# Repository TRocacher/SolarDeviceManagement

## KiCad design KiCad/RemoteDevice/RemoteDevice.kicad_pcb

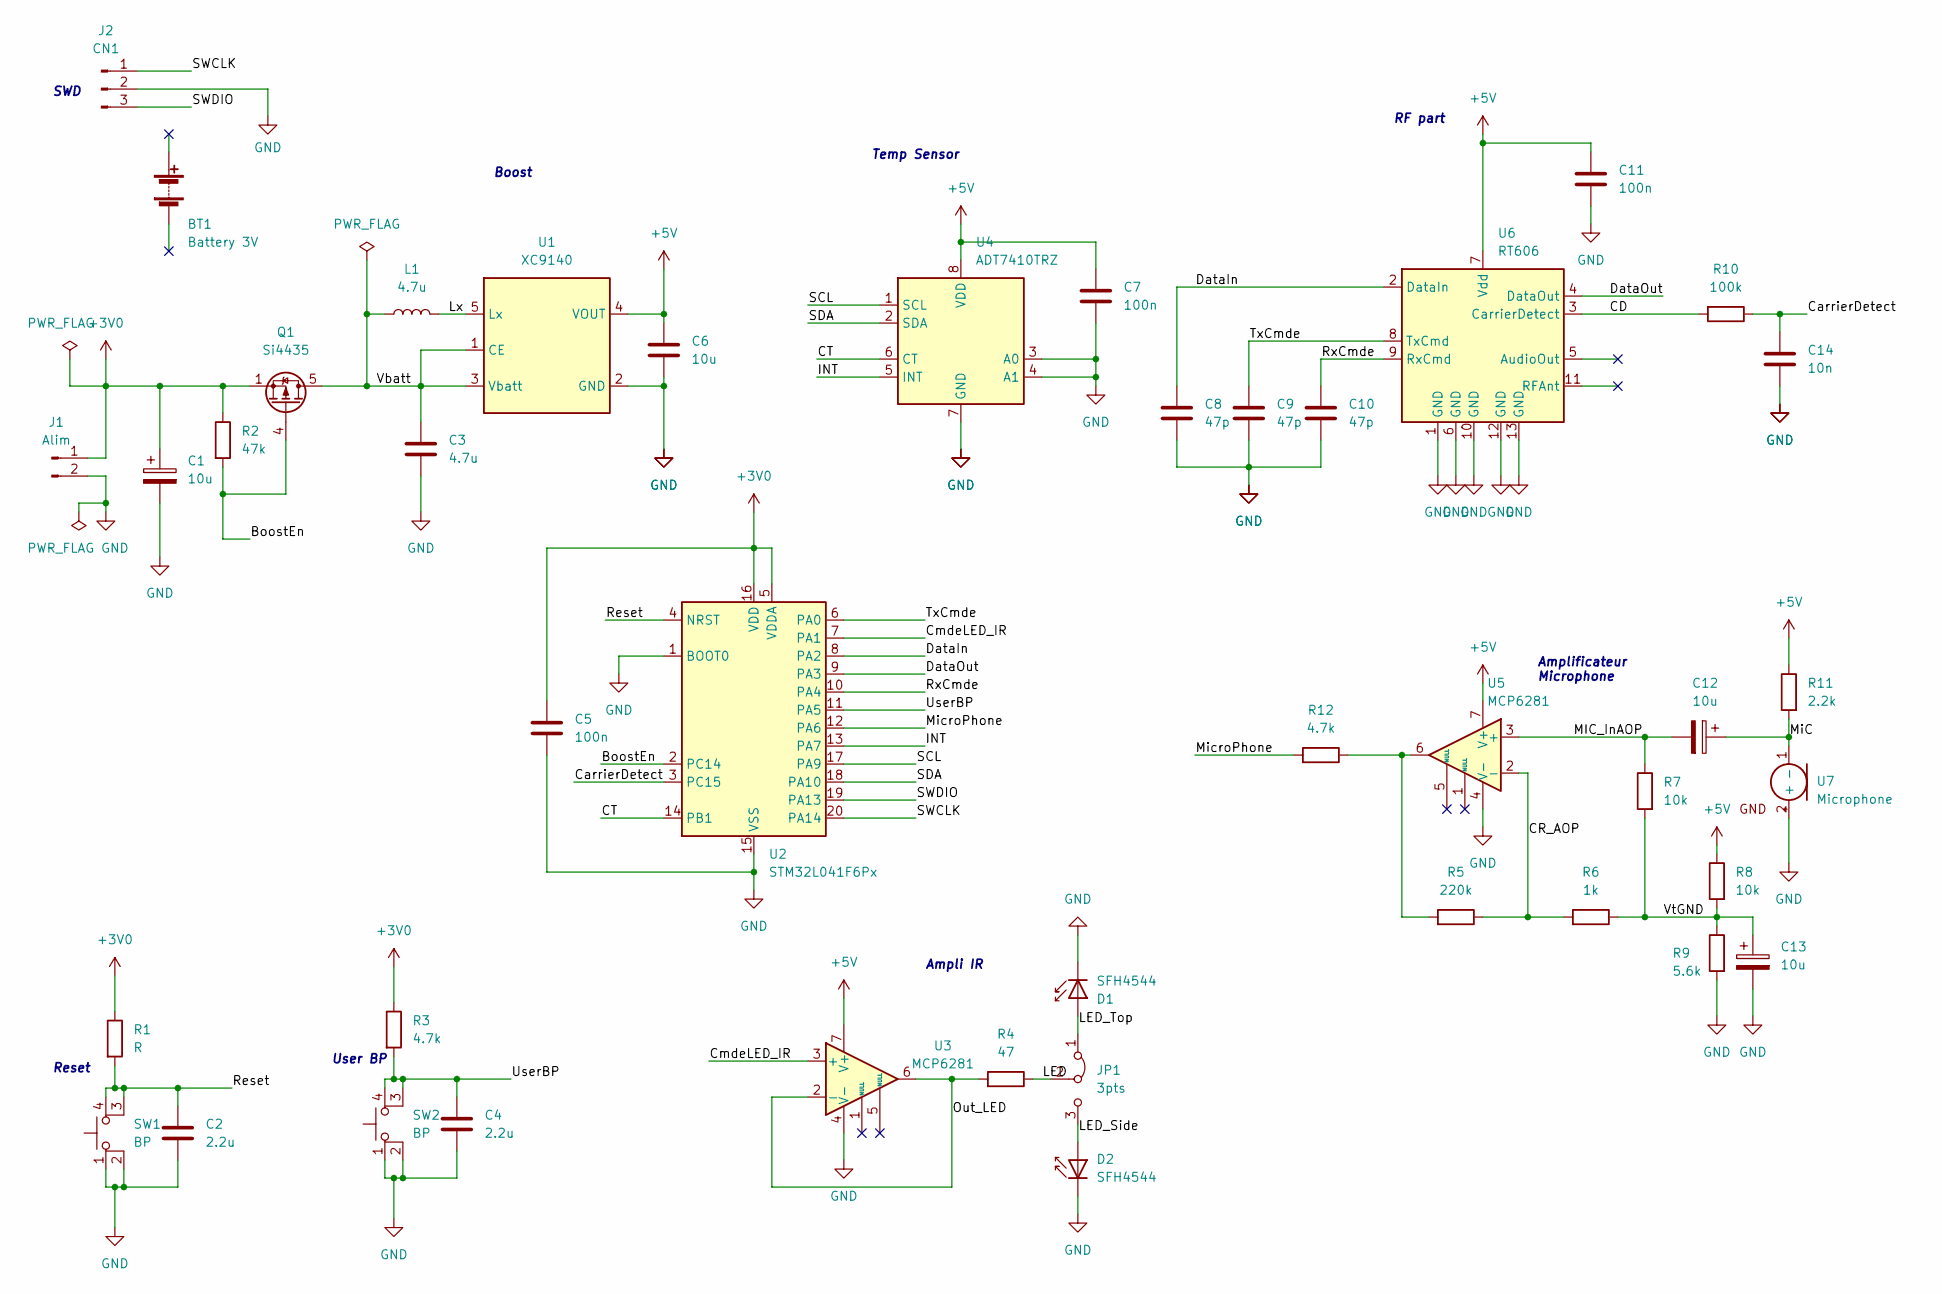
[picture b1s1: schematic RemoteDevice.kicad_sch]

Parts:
BT1: Battery 3V; BatteryHolder_Keystone_2468_2xAAA
C1, C12, C13: 10u; CP_EIA-7132-20_AVX-U
C2, C4: 2.2u; C_1812_4532Metric
C3: 4.7u; C_1812_4532Metric
C5, C7, C11: 100n; C_1206_3216Metric
C6: 10u; C_1812_4532Metric
C8, C9, C10: 47p; C_0805_2012Metric
C14: 10n; C_1206_3216Metric
D1, D2: SFH4544; LED_D5.0mm_IRGrey
J1: Alim; PinHeader2pts
J2: CN1; PinHeader3pts
JP1: 3pts; PinHeader3pts
L1: 4.7u; L_Abracon_ASPI-3012S
Q1: Si4435; PowerPAK_SO-8_Single
R1: R; R_1206_3216Metric
R2: 47k; R_1206_3216Metric
R3, R12: 4.7k; R_1206_3216Metric
R4: 47; R_1206_3216Metric
R5: 220k; R_1206_3216Metric
R6: 1k; R_1206_3216Metric
R7, R8: 10k; R_1206_3216Metric
R9: 5.6k; R_1206_3216Metric
R10: 100k; R_1206_3216Metric
R11: 2.2k; R_1206_3216Metric
SW1, SW2: BP; SW
U1: XC9140; SOT-23-5
U2: STM32L041F6Px; TSSOP-20_4.4x6.5mm_P0.65mm
U3, U5: MCP6281; SOIC-8_3.9x4.9mm_P1.27mm
U4: ADT7410TRZ; SOP-8_3.9x4.9mm_P1.27mm
U6: RT606
U7: Microphone

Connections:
+3V0: C1.1, C5.1, J1.1, Q1.1 (S), Q1.2 (S), Q1.3 (S), R1.1, R2.1, R3.1, U2.5 (VDDA), U2.16 (VDD)
+5V: C6.1, C7.1, C11.1, R8.1, R11.1, U1.4 (VOUT), U3.7 (V+), U4.8 (VDD), U5.7 (V+), U6.7 (Vdd)
/BoostEn: Q1.4 (G), R2.2, U2.2 (PC14)
/CD: R10.2, U6.3 (CarrierDetect)
/CR_AOP: R5.1, R6.2, U5.2 (-)
/CT: U2.14 (PB1), U4.6 (CT)
/CarrierDetect: C14.1, R10.1, U2.3 (PC15)
/CmdeLED_IR: U2.7 (PA1), U3.3 (+)
/DataIn: C8.1, U2.8 (PA2), U6.2 (DataIn)
/DataOut: U2.9 (PA3), U6.4 (DataOut)
/INT: U2.13 (PA7), U4.5 (INT)
/LED: JP1.2 (C), R4.1
/LED_Side: D2.2 (A), JP1.3 (B)
/LED_Top: D1.2 (A), JP1.1 (A)
/Lx: L1.1, U1.5 (Lx)
/MIC_InAOP: C12.2, R7.1, U5.3 (+)
/MiC: C12.1, R11.2, U7.1 (-)
/MicroPhone: R12.2, U2.12 (PA6)
/Out_LED: R4.2, U3.2 (-), U3.6
/Reset: C2.1, R1.2, SW1.3, SW1.4, U2.4 (NRST)
/RxCmde: C10.1, U2.10 (PA4), U6.9 (RxCmd)
/SCL: U2.17 (PA9), U4.1 (SCL)
/SDA: U2.18 (PA10), U4.2 (SDA)
/SWCLK: J2.1, U2.20 (PA14)
/SWDIO: J2.3, U2.19 (PA13)
/TxCmde: C9.1, U2.6 (PA0), U6.8 (TxCmd)
/UserBP: C4.1, R3.2, SW2.3, SW2.4, U2.11 (PA5)
/Vbatt: C3.1, L1.2, Q1.5 (D), U1.1 (CE), U1.3 (Vbatt)
/VtGND: C13.1, R6.1, R7.2, R8.2, R9.1
GND: C1.2, C2.2, C3.2, C4.2, C5.2, C6.2, C7.2, C8.2, C9.2, C10.2, C11.2, C13.2, C14.2, D1.1 (K), D2.1 (K), J1.2, J2.2, R9.2, SW1.1, SW1.2, SW2.1, SW2.2, U1.2 (GND), U2.1 (BOOT0), U2.15 (VSS), U3.4 (V-), U4.3 (A0), U4.4 (A1), U4.7 (GND), U5.4 (V-), U6.1 (GND), U6.6 (GND), U6.10 (GND), U6.12 (GND), U6.13 (GND), U7.2 (+)
unnamed: R5.2, R12.1, U5.6

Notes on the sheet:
Ampli IR
Boost
Reset
RF part
Amplificateur Microphone
Temp Sensor
User BP
SWD

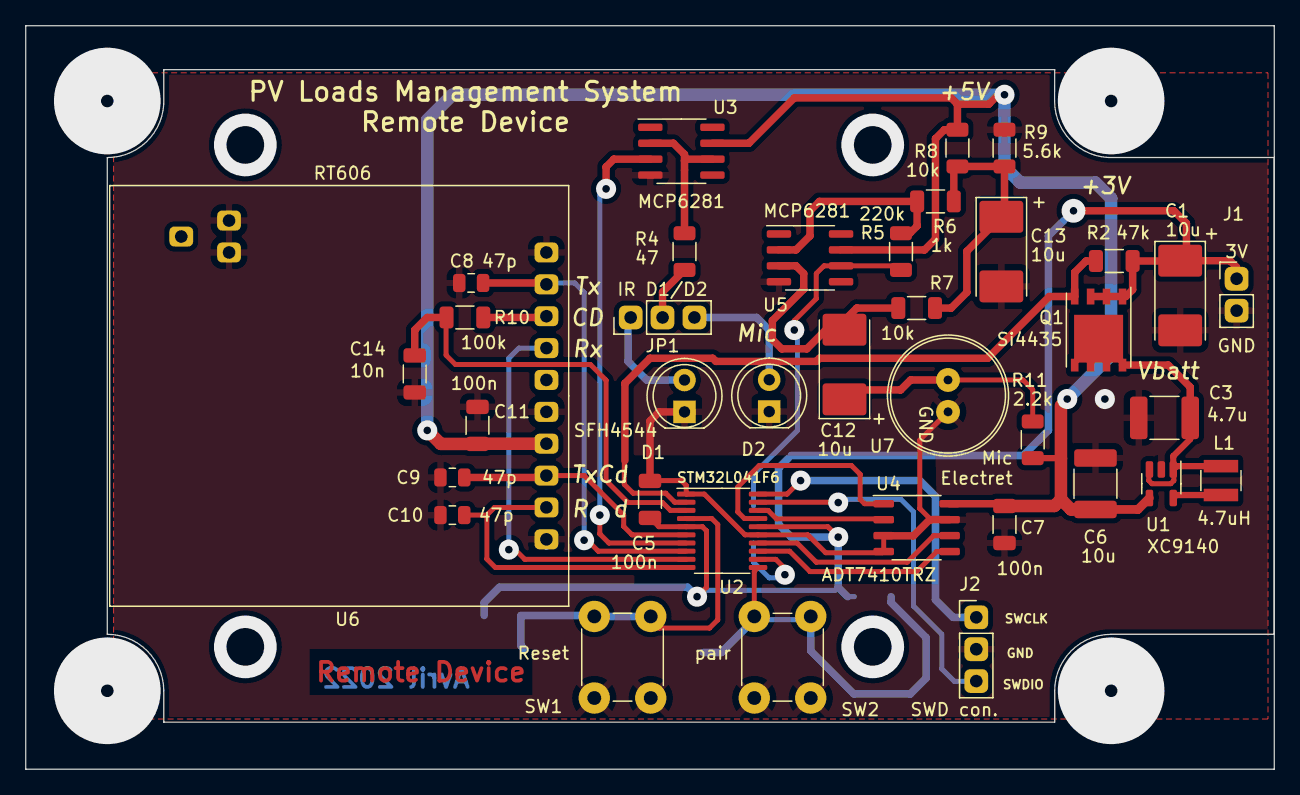
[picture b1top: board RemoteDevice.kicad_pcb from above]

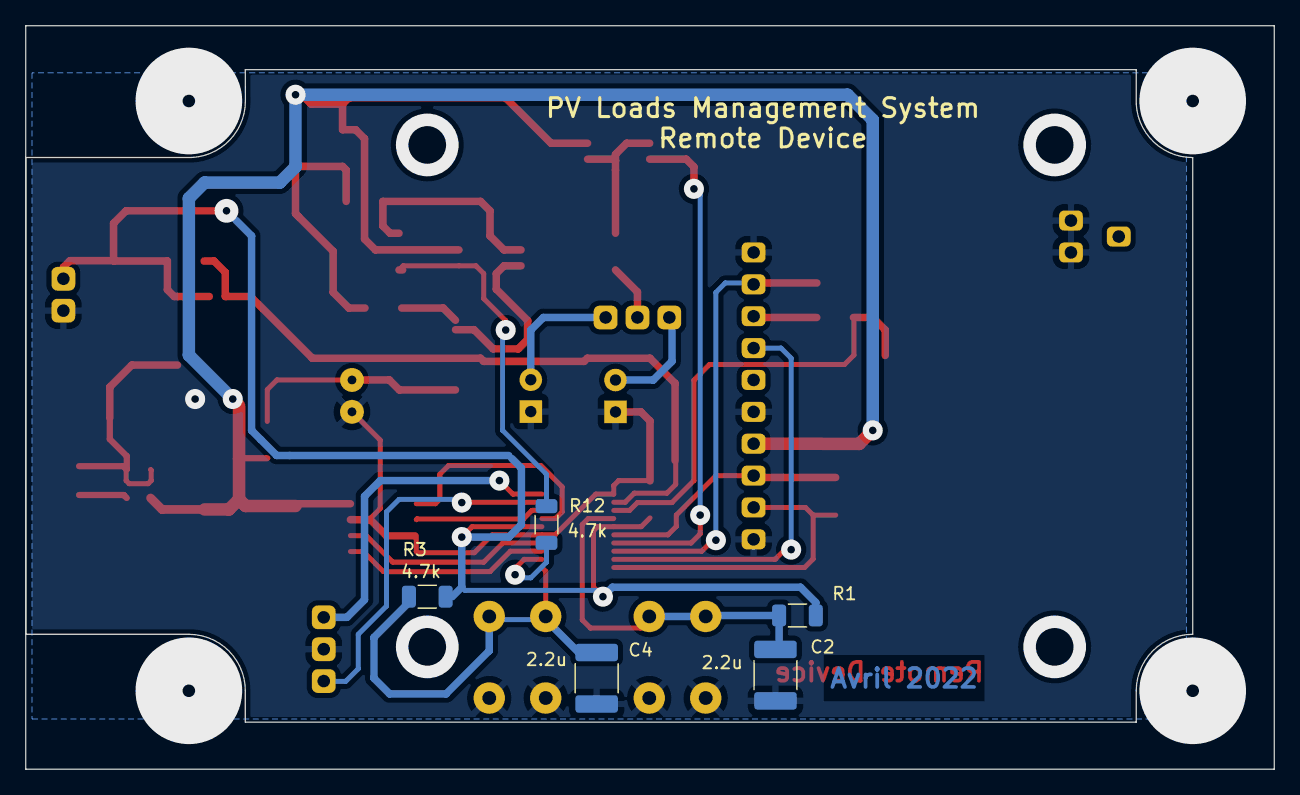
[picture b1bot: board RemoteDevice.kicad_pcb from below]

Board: 2 copper layers, 99.5 x 59.2 mm, 42 parts (5 on the bottom side), 31 nets.

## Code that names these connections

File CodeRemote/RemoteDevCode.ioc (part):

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PA6.Mode=IN6
Mcu.UserName=STM32L041F6Px
PC14-OSC32_IN.Signal=GPIO_Output
PA3.Mode=Asynchronous
PA13.Signal=SYS_SWDIO
PA9.Signal=I2C1_SCL
PC15-OSC32_OUT.Signal=GPIO_Input
PA1.Signal=S_TIM2_CH2
PA5.Signal=GPIO_Input
RCC.HSE_VALUE=8000000
board=custom
PA0-CK_IN.Signal=GPIO_Output
PA14.Mode=Serial_Wire
PA13.Mode=Serial_Wire
Mcu.Name=STM32L041F6Px
PA2.Signal=USART2_TX
PA4.Signal=GPIO_Output
RCC.SYSCLKFreq_VALUE=2097000
Mcu.Package=TSSOP20
PB1.Signal=GPIO_Input
PA6.Signal=ADC_IN6
PA10.Signal=I2C1_SDA
PA14.Signal=SYS_SWCLK
PA2.Mode=Asynchronous
PA3.Signal=USART2_RX
PA7.Signal=GPIO_Input

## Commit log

2022-01-09 Demarrage difficile. Algo dans le .odt. Code conforme mais typiquement le timer tourne à 480µs au lieu de 430 mesuré avec Discov. A débugger.
2022-01-10 Bug trouvé, PLL mal configurée dans CubeMx. Poursuivre le débugage et la mise au point
2022-01-10 Synchro Sample OK, Validation détection 19 deg et 20 deg par 3 essais de suite. Réfléchir à un système propre pour sniffer tous les codes...
2022-01-31 Pgm hack code OK, avec mode d emploi dans .odt. Code craqués dans un .txt pour mitsubishi. A faire : émetteur pour valider POC
2022-02-03 Premiers essais Xbee et FSK. Attention Pb boitier FSK prévu uniquement pour 9600 Bds. Xbee portée bureau-porte garage. FSK OK full distance. Attention Antenne
2022-02-03 programme reception : trame d'envoie codée par ##### parsée, chaîne extraite, cad suppression caractères pourris d'entête ainsi que les #
2022-02-06 emetteur et récepteur STM en cours. Test à 38400 Bds entre bureau et garage, pas mal. Chercher la différence entre l'archi de Seb et la mienne
2022-02-07 Filtrage soft modifié, avec 3, 4 ou 5#. Filtrage CD avec filtre, encore des 1/10 d'erreur. Idee : modif UART, chercher ### plutôt que CR. A voir
2022-02-11 version avec détection ##### puis 2 octets CRC puis 16 octets de data -> modifs faites dans driver UART, version b. Validé réele COM série XCTU
2022-02-12 first commit, mise en place SMachine....
2022-02-12 SM OK, détection ##### avec 0 erreur sur 6300 à 2m de distance, pas d'utilisation CD. Check Sum à faire
2022-02-12 CheckSum et Timeout OK. Validée longue distance (clim salon-garage). Quelques ratés mais pas d'erreur CRC. Allonger l'entête avant ##### pour améliorer.
2022-02-13 Code stop émis lors d'appuis sur User BP. La forme d'onde a l'air bonne sur Analog Discovery. Tester l'interface LED... puis autres codes...
2022-02-14 Gestion LCD ajoutée. Output sur PC9 car PC11 est utilisé par le LCD. Echec test clim, changer LED IR l=950nm. Autre codes teleco à implémenter
2022-02-15 Code clone OK, sur BP, on va de stop à chaud 18 à 23. Les codes sont testés sur récepteur, photos dispo ds CmdeClim. Tester 950nm, ajuster Tsymbole si besoin, voir photos
2022-02-17 Teleco OK, avec diode de la TV sony et MODULATION OOK 38kHz git logg Sortie sur PA0 avec PWM 38kHz on/off. Le clone est opérationnel !
2022-04-07 Schema OK, association en cours, faire le micro électret
2022-04-09 Edge cut OK, le compartiment de pile ne fait pas partie du brd (car pb en épaisseur). Placement commencé
2022-04-09 routage bien avancé. Vérifier remap harmoniser odt. Reprendre pack RT606 pour passer cuivre entre pastille
2022-04-12 paxkagez RT606 OK, remap à contrôler, routage presque entièrement dégrossi, pb DRC sur edge cut
2022-04-12 Routage très avancé, pb edge cut réglé, remap à vérifier, silkscreen OK sur cmp name
2022-04-13 suppression des warning et erreurs, il en reste mais pas grave. Vérifier remap
2022-04-13 Revue des plans de masses pour qu'ils prennent une forme arrondie automatiquement avec edge cut, remap check IO OK, vérifié avec CubeMx 32L041F6
2022-04-14 Version béta, production josé GEI, ajout d'une résistance série sur le micro pour ne pas griller l'IO (5V max)
2022-04-21 Version PCB réalisée au GEI. Des améliorations sont à apporter, voir Amelioration_PCB.txt
